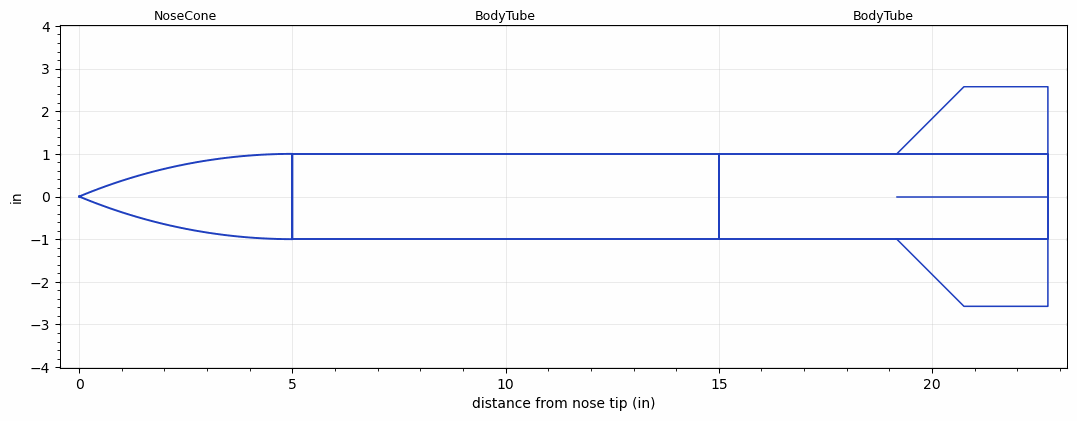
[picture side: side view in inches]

<RASAeroDocument>
 <FileVersion>2</FileVersion>
 <RocketDesign>
  <NoseCone>
   <Length>5</Length>
   <Diameter>2</Diameter>
   <Shape>Tangent Ogive</Shape>
   <Location>0</Location>
  </NoseCone>
  <BodyTube>
   <Length>10</Length>
   <Diameter>2</Diameter>
   <Location>5</Location>
  </BodyTube>
  <BodyTube>
   <Length>7.716536</Length>
   <Diameter>2</Diameter>
   <Location>15</Location>
   <Fin>
    <Count>4</Count>
    <Chord>3.543307</Chord>
    <Span>1.574803</Span>
    <SweepDistance>1.574803</SweepDistance>
    <TipChord>1.968504</TipChord>
    <Thickness>0.07874016</Thickness>
    <Location>3.543307</Location>
    <AirfoilSection>Square</AirfoilSection>
   </Fin>
  </BodyTube>
  <Surface>Sheet Metal</Surface>
  <ModifiedBarrowman>False</ModifiedBarrowman>
  <Turbulence>False</Turbulence>
  <UseBooster1>False</UseBooster1>
  <UseBooster2>False</UseBooster2>
 </RocketDesign>
 <LaunchSite>
  <Altitude>0</Altitude>
  <Pressure>0</Pressure>
  <RodAngle>0</RodAngle>
  <RodLength>4</RodLength>
  <Temperature>74</Temperature>
  <WindSpeed>0</WindSpeed>
 </LaunchSite>
 <Recovery>
  <Altitude1>1000</Altitude1>
  <Altitude2>1000</Altitude2>
  <DeviceType1>None</DeviceType1>
  <DeviceType2>None</DeviceType2>
  <Event1>False</Event1>
  <Event2>False</Event2>
  <Size1>1</Size1>
  <Size2>1</Size2>
  <EventType1>None</EventType1>
  <EventType2>None</EventType2>
  <CD1>1.33</CD1>
  <CD2>1.33</CD2>
 </Recovery>
 <SimulationList>
  <Simulation>
   <SustainerEngine>E6  (AT)</SustainerEngine>
   <SustainerLaunchWt>0.66</SustainerLaunchWt>
   <SustainerNozzleDiameter>0.2</SustainerNozzleDiameter>
   <SustainerCG>11.5</SustainerCG>
   <SustainerIgnitionDelay>0</SustainerIgnitionDelay>
   <Booster1SeparationDelay>0</Booster1SeparationDelay>
   <Booster1IgnitionDelay>0</Booster1IgnitionDelay>
   <IncludeBooster1>False</IncludeBooster1>
   <Booster2Delay>0</Booster2Delay>
   <IncludeBooster2>False</IncludeBooster2>
   <TimetoApogee>10.81015</TimetoApogee>
   <MaxAltitude>1221.319</MaxAltitude>
   <MaxVelocity>186.4011</MaxVelocity>
   <OptimumWt>0.1320001</OptimumWt>
   <OptimumMaxAlt>0.1320001</OptimumMaxAlt>
  </Simulation>
 </SimulationList>
</RASAeroDocument>
